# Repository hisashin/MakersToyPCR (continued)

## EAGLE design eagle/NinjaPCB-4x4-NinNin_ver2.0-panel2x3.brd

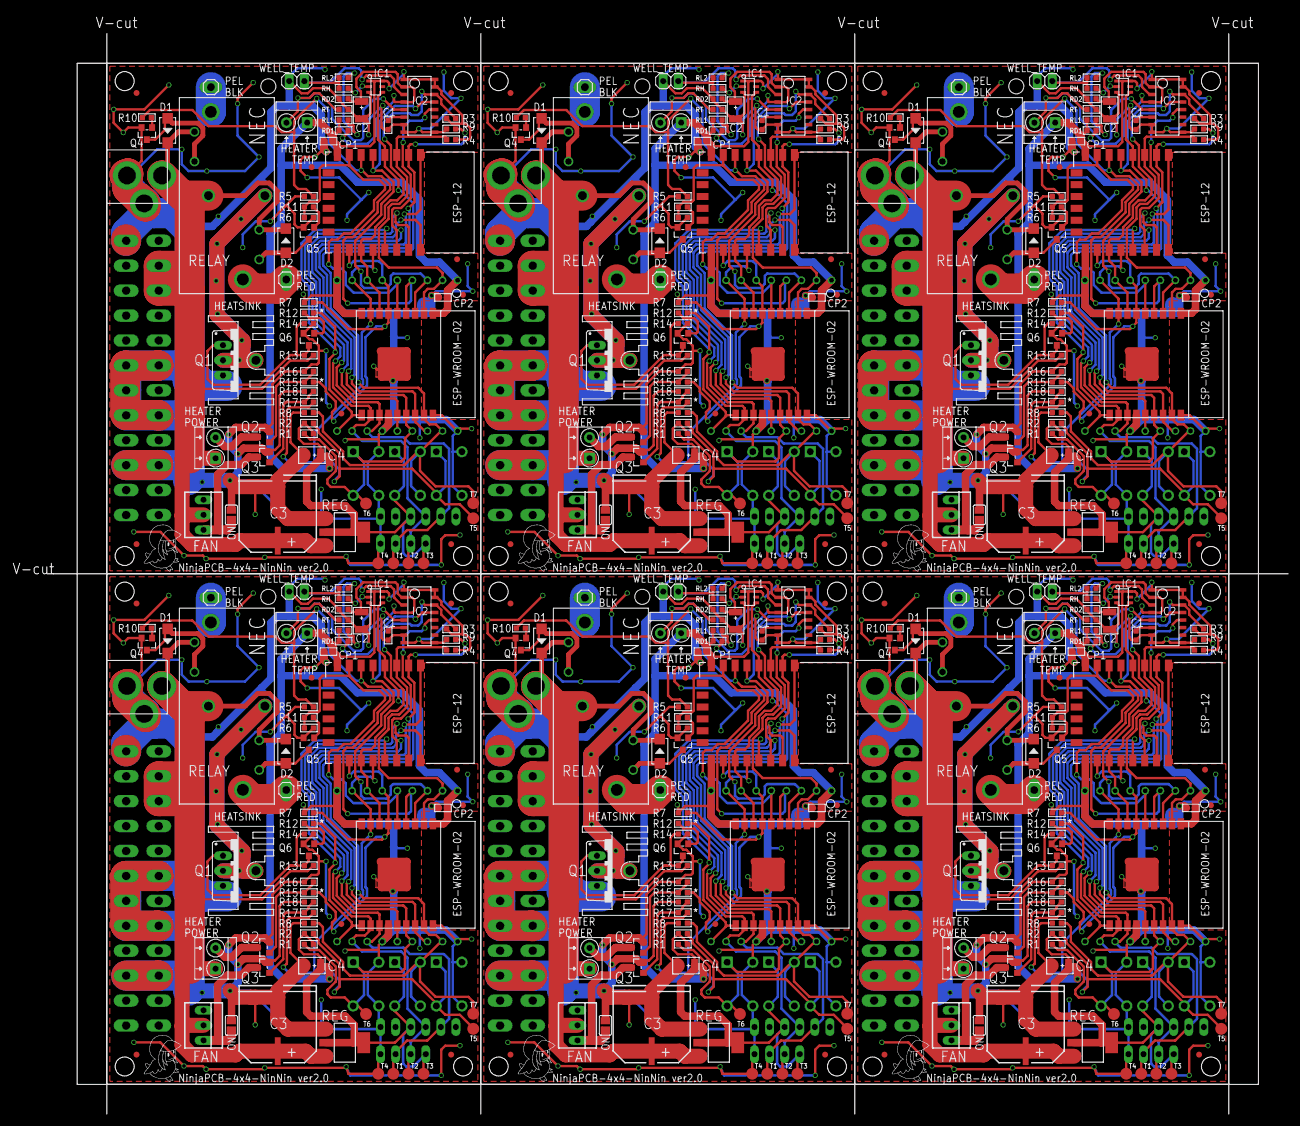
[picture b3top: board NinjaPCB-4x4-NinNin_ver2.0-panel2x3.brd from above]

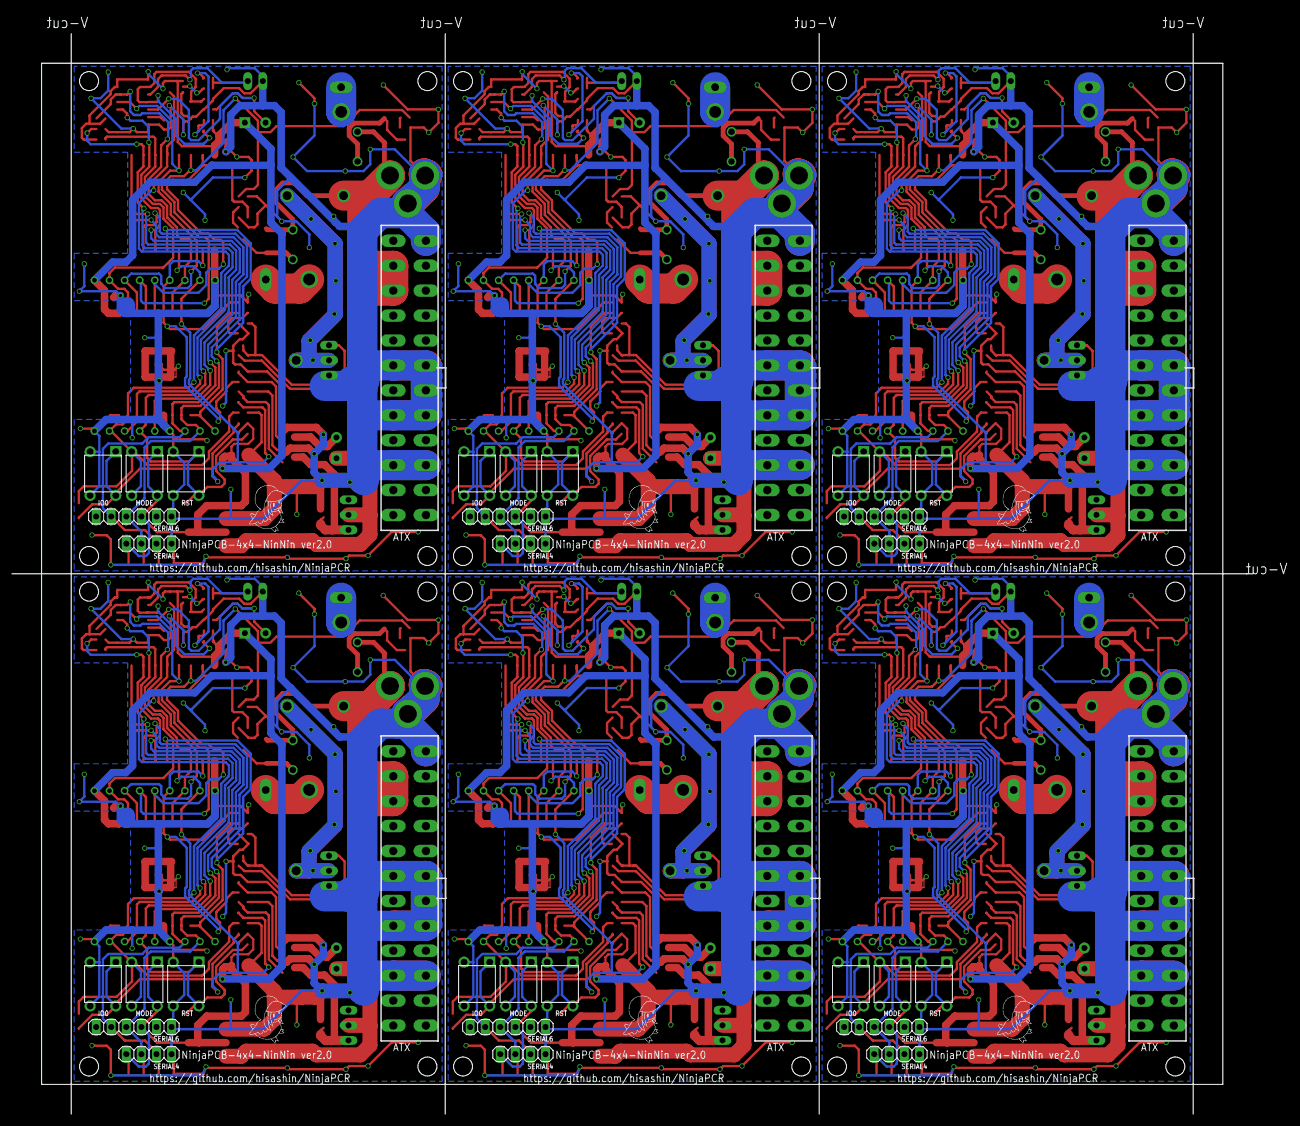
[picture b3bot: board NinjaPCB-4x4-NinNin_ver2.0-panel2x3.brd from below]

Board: 2 copper layers, 209.0 x 182.0 mm, 462 parts (42 on the bottom side), 216 nets.

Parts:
ATX, ATX1, ATX2, ATX3, ATX4, ATX5: ATX24NH; ATX24
C1, C7, C11, C15, C19, C23: 100nf; C0603
C2, C4, C5, C8, C9, C12, C13, C16, C17, C20, C21, C24: 22uf; AVX-B
C3, C6, C10, C14, C18, C22: CAP_SMDAL_1000UF_25V; CAP_SMD_AL_D125
CP1, CP2, CP3, CP4, CP5, CP6, CP7, CP8, CP9, CP10, CP11, CP12: 100nf; C0603
D1, D2, D3, D4, D5, D6, D7, D8, D9, D10, D11, D12: 1N4007; DO-214AC
ESP-1, ESP-2, ESP-3, ESP-4, ESP-5, ESP-12: ESP-12F
ESP-WROOM-01, ESP-WROOM-02, ESP-WROOM-03, ESP-WROOM-04, ESP-WROOM-05, ESP-WROOM-06: ESP-WROOM-02
ESP-WROOM-02-BREAK, ESP-WROOM-02-BREAK1, ESP-WROOM-02-BREAK2, ESP-WROOM-02-BREAK3, ESP-WROOM-02-BREAK4, ESP-WROOM-02-BREAK5: ESP-WROOM-02-BREAKND; ESP-WROOM-02-BREAK-NODETAIL
FAN, FAN1, FAN2, FAN3, FAN4, FAN5: 22-23-2031
FAN_ON, FAN_ON1, FAN_ON2, FAN_ON3, FAN_ON4, FAN_ON5: SJ
HEATER_POWER, HEATER_POWER1, HEATER_POWER2, HEATER_POWER3, HEATER_POWER4, HEATER_POWER5: H2-3.5-7.0X7.0MM
HEATER_TEMP, HEATER_TEMP1, HEATER_TEMP2, HEATER_TEMP3, HEATER_TEMP4, HEATER_TEMP5: H2-3.5-7.0X7.0MM
HEATSINK, HEATSINK1, HEATSINK2, HEATSINK3, HEATSINK4, HEATSINK5: HEAT111PB015; HEAT11PB015
IC1, IC4, IC6, IC8, IC10, IC12: ANALOGSW_AD_SOT23-6; SOT-23-6
IC2, IC3, IC5, IC7, IC9, IC11: NAU7802; SOP-16
IO0, IO1, IO2, IO3, IO4, IO5: SW4-6.0X6.0X5.0MM
JACK, JACK1, JACK2, JACK3, JACK4, JACK5: 2.1MMJACKTHM-NOOUT; PJ-102A-NOOUT
MODE, MODE1, MODE2, MODE3, MODE4, MODE5: SW4-6.0X6.0X5.0MM
PEL_BLK, PEL_BLK1, PEL_BLK2, PEL_BLK3, PEL_BLK4, PEL_BLK5: 1X01LONG
PEL_RED, PEL_RED1, PEL_RED2, PEL_RED3, PEL_RED4, PEL_RED5: 1X01LONG
Q1, Q12, Q18, Q24, Q30, Q36: IRLB3813PBF; TO220BV
Q2, Q3, Q10, Q11, Q16, Q17, Q22, Q23, Q28, Q29, Q34, Q35: CJ2302; SOT-23
Q4, Q5, Q6, Q7, Q8, Q9, Q13, Q14, Q15, Q19, Q20, Q21, Q25, Q26, Q27, Q31, Q32, Q33: S9013; SOT-23
R1, R2, R3, R4, R5, R6, R7, R8, R9, R10, R11, R13, R14, R16, R18, R19, R22, R23, R24, R25, R26, R28, R29, R30, R31, R32, R33, R34, R35, R36, R37, R40, R41, R42, R43, R44, R46, R47, R48, R49, R50, R51, R52, R53, R54, R55, R58, R59, R60, R61, R62, R64, R65, R66, R67, R68, R69, R70, R71, R72, R73, R76, R77, R78, R79, R80, R82, R83, R84, R85, R86, R87, R88, R89, R90, R91, R94, R95, R96, R97, R98, R100, R101, R102, R103, R104, R105, R106, R107, R108: 10K 1/10W; R0603
R12, R15, R17, R20, R21, R27, R38, R39, R45, R56, R57, R63, R74, R75, R81, R92, R93, R99: 1K 1/10W; R0603
RD1, RD2, RD3, RD4, RD5, RD6, RD7, RD8, RD9, RD10, RD11, RD12: 15K HP; R0603
REG, REG1, REG2, REG3, REG4, REG5: CJT1117-3.3-SOT223; SOT-223
RELAY, RELAY1, RELAY2, RELAY3, RELAY4, RELAY5: NEC-RELAY2EP2; NEC-EP2
RH, RH1, RH2, RH3, RH4, RH5: 15K HP; R0603
RL1, RL2, RL3, RL4, RL5, RL6, RL7, RL8, RL9, RL10, RL11, RL12: 15K HP; R0603
RST, RST1, RST2, RST3, RST4, RST5: SW4-6.0X6.0X5.0MM
RT, RT1, RT2, RT3, RT4, RT5: 15K HP; R0603
SERIAL1, SERIAL3, SERIAL6, SERIAL7, SERIAL9, SERIAL11: 1X06
SERIAL2, SERIAL4, SERIAL5, SERIAL8, SERIAL10, SERIAL12: 1X04
T1, T2, T3, T4, T5, T6, T7, T8, T9, T10, T11, T12, T13, T14, T15, T16, T17, T18, T19, T20, T21, T22, T23, T24, T25, T26, T27, T28, T29, T30, T31, T32, T33, T34, T35, T36, T37, T38, T39, T40, T41, T42: TPTP20R; TP20R
U$1, U$2, U$15, U$16, U$25, U$26, U$35, U$36, U$45, U$46, U$55, U$56: TORI_0.25
U$3, U$4, U$5, U$6, U$7, U$8, U$9, U$10, U$11, U$12, U$13, U$14, U$17, U$18, U$19, U$20, U$21, U$22, U$23, U$24, U$27, U$28, U$29, U$30, U$31, U$32, U$33, U$34, U$37, U$38, U$39, U$40, U$41, U$42, U$43, U$44, U$47, U$48, U$49, U$50, U$51, U$52, U$53, U$54, U$57, U$58, U$59, U$60: FIDUCIAL; FIDUCIAL_1MM
WELL_TEMP, WELL_TEMP1, WELL_TEMP2, WELL_TEMP3, WELL_TEMP4, WELL_TEMP5: 1X02

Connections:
3V1: C5.+, CP3.1, CP4.2, ESP-1.8, ESP-WROOM-01.P$1, ESP-WROOM-02-BREAK1.P$1, HEATER_TEMP1.1, IC3.P$1, IC3.P$15, IC3.P$16, IC4.P$1, IC4.P$6, MODE1.1, MODE1.4, R19.1, R23.1, R32.1, R35.1, RD3.2, REG1.2, REG1.TER, RL4.1, SERIAL1.4, SERIAL2.1, T10.TP
3V2: C9.+, CP5.1, CP6.2, ESP-2.8, ESP-WROOM-02-BREAK2.P$1, ESP-WROOM-03.P$1, HEATER_TEMP2.1, IC5.P$1, IC5.P$15, IC5.P$16, IC6.P$1, IC6.P$6, MODE2.1, MODE2.4, R37.1, R41.1, R50.1, R53.1, RD5.2, REG2.2, REG2.TER, RL6.1, SERIAL3.4, SERIAL5.1, T17.TP
3V3: C4.+, CP1.1, CP2.2, ESP-12.8, ESP-WROOM-02.P$1, ESP-WROOM-02-BREAK.P$1, HEATER_TEMP.1, IC1.P$1, IC1.P$6, IC2.P$1, IC2.P$15, IC2.P$16, MODE.1, MODE.4, R1.1, R2.1, R3.1, R4.1, RD1.2, REG.2, REG.TER, RL1.1, SERIAL4.1, SERIAL6.4, T3.TP
3V4: C13.+, CP7.1, CP8.2, ESP-3.8, ESP-WROOM-02-BREAK3.P$1, ESP-WROOM-04.P$1, HEATER_TEMP3.1, IC7.P$1, IC7.P$15, IC7.P$16, IC8.P$1, IC8.P$6, MODE3.1, MODE3.4, R55.1, R59.1, R68.1, R71.1, RD7.2, REG3.2, REG3.TER, RL8.1, SERIAL7.4, SERIAL8.1, T24.TP
3V5: C17.+, CP9.1, CP10.2, ESP-4.8, ESP-WROOM-02-BREAK4.P$1, ESP-WROOM-05.P$1, HEATER_TEMP4.1, IC9.P$1, IC9.P$15, IC9.P$16, IC10.P$1, IC10.P$6, MODE4.1, MODE4.4, R73.1, R77.1, R86.1, R89.1, RD9.2, REG4.2, REG4.TER, RL10.1, SERIAL9.4, SERIAL10.1, T31.TP
3V6: C21.+, CP11.1, CP12.2, ESP-5.8, ESP-WROOM-02-BREAK5.P$1, ESP-WROOM-06.P$1, HEATER_TEMP5.1, IC11.P$1, IC11.P$15, IC11.P$16, IC12.P$1, IC12.P$6, MODE5.1, MODE5.4, R91.1, R95.1, R104.1, R107.1, RD11.2, REG5.2, REG5.TER, RL12.1, SERIAL11.4, SERIAL12.1, T38.TP
12V: ATX.10, ATX.11, C3.P$P, D1.2, D2.2, FAN.2, HEATER_POWER.1, JACK.TIP, R13.2, REG.3, RELAY.P$2, RELAY.P$4, RELAY.P$6
12V1: ATX1.10, ATX1.11, C6.P$P, D3.2, D4.2, FAN1.2, HEATER_POWER1.1, JACK1.TIP, R28.2, REG1.3, RELAY1.P$2, RELAY1.P$4, RELAY1.P$6
12V2: ATX2.10, ATX2.11, C10.P$P, D5.2, D6.2, FAN2.2, HEATER_POWER2.1, JACK2.TIP, R46.2, REG2.3, RELAY2.P$2, RELAY2.P$4, RELAY2.P$6
12V3: ATX3.10, ATX3.11, C14.P$P, D7.2, D8.2, FAN3.2, HEATER_POWER3.1, JACK3.TIP, R64.2, REG3.3, RELAY3.P$2, RELAY3.P$4, RELAY3.P$6
12V4: ATX4.10, ATX4.11, C18.P$P, D9.2, D10.2, FAN4.2, HEATER_POWER4.1, JACK4.TIP, R82.2, REG4.3, RELAY4.P$2, RELAY4.P$4, RELAY4.P$6
12V5: ATX5.10, ATX5.11, C22.P$P, D11.2, D12.2, FAN5.2, HEATER_POWER5.1, JACK5.TIP, R100.2, REG5.3, RELAY5.P$2, RELAY5.P$4, RELAY5.P$6
DIVIDED: C2.+, IC2.P$2, IC2.P$4, RD1.1, RD2.1
DIVIDED1: C8.+, IC3.P$2, IC3.P$4, RD3.1, RD4.1
DIVIDED2: C12.+, IC5.P$2, IC5.P$4, RD5.1, RD6.1
DIVIDED3: C16.+, IC7.P$2, IC7.P$4, RD7.1, RD8.1
DIVIDED4: C20.+, IC9.P$2, IC9.P$4, RD9.1, RD10.1
DIVIDED5: C24.+, IC11.P$2, IC11.P$4, RD11.1, RD12.1
DRDY: ESP-12.20, ESP-WROOM-02.P$14, ESP-WROOM-02-BREAK.P$14, IC2.P$12
DRDY1: ESP-1.20, ESP-WROOM-01.P$14, ESP-WROOM-02-BREAK1.P$14, IC3.P$12
DRDY2: ESP-2.20, ESP-WROOM-02-BREAK2.P$14, ESP-WROOM-03.P$14, IC5.P$12
DRDY3: ESP-3.20, ESP-WROOM-02-BREAK3.P$14, ESP-WROOM-04.P$14, IC7.P$12
DRDY4: ESP-4.20, ESP-WROOM-02-BREAK4.P$14, ESP-WROOM-05.P$14, IC9.P$12
DRDY5: ESP-5.20, ESP-WROOM-02-BREAK5.P$14, ESP-WROOM-06.P$14, IC11.P$12
EN: ESP-12.3, ESP-WROOM-02.P$2, ESP-WROOM-02-BREAK.P$2, R4.2
EN1: ESP-1.3, ESP-WROOM-01.P$2, ESP-WROOM-02-BREAK1.P$2, R32.2
EN2: ESP-2.3, ESP-WROOM-02-BREAK2.P$2, ESP-WROOM-03.P$2, R50.2
EN3: ESP-3.3, ESP-WROOM-02-BREAK3.P$2, ESP-WROOM-04.P$2, R68.2
EN4: ESP-4.3, ESP-WROOM-02-BREAK4.P$2, ESP-WROOM-05.P$2, R86.2
EN5: ESP-5.3, ESP-WROOM-02-BREAK5.P$2, ESP-WROOM-06.P$2, R104.2
FAN: ESP-12.18, ESP-WROOM-02.P$8, ESP-WROOM-02-BREAK.P$8, IO0.1, IO0.4, R2.2, R17.1, T5.TP
FAN1: ESP-1.18, ESP-WROOM-01.P$8, ESP-WROOM-02-BREAK1.P$8, IO1.1, IO1.4, R20.1, R23.2, T12.TP
FAN2: ESP-2.18, ESP-WROOM-02-BREAK2.P$8, ESP-WROOM-03.P$8, IO2.1, IO2.4, R38.1, R41.2, T19.TP
FAN3: ESP-3.18, ESP-WROOM-02-BREAK3.P$8, ESP-WROOM-04.P$8, IO3.1, IO3.4, R56.1, R59.2, T26.TP
FAN4: ESP-4.18, ESP-WROOM-02-BREAK4.P$8, ESP-WROOM-05.P$8, IO4.1, IO4.4, R74.1, R77.2, T33.TP
FAN5: ESP-5.18, ESP-WROOM-02-BREAK5.P$8, ESP-WROOM-06.P$8, IO5.1, IO5.4, R92.1, R95.2, T40.TP
GND: ATX.3, ATX.5, ATX.7, ATX.15, ATX.17, ATX.18, ATX.19, ATX.24, C1.1, C2.-, C3.P$M, C4.-, CP1.2, CP2.1, ESP-12.15, ESP-WROOM-02.P$9, ESP-WROOM-02.P$13, ESP-WROOM-02.P$18, ESP-WROOM-02.P$19, ESP-WROOM-02-BREAK.P$9, ESP-WROOM-02-BREAK.P$13, ESP-WROOM-02-BREAK.P$18, FAN_ON.1, IC1.P$3, IC2.P$7, IC2.P$8, IC2.P$9, IO0.2, IO0.3, JACK.RING, JACK.RING_SW, Q1.S, Q2.2, Q3.2, Q4.2, Q5.2, Q6.2, R5.1, R6.1, R7.1, R8.1, R9.1, R14.1, R16.1, R18.1, RD2.2, REG.1, RST.2, RST.3, RT.2, SERIAL4.4, SERIAL6.6, T4.TP, WELL_TEMP.2
GND1: ATX1.3, ATX1.5, ATX1.7, ATX1.15, ATX1.17, ATX1.18, ATX1.19, ATX1.24, C5.-, C6.P$M, C7.1, C8.-, CP3.2, CP4.1, ESP-1.15, ESP-WROOM-01.P$9, ESP-WROOM-01.P$13, ESP-WROOM-01.P$18, ESP-WROOM-01.P$19, ESP-WROOM-02-BREAK1.P$9, ESP-WROOM-02-BREAK1.P$13, ESP-WROOM-02-BREAK1.P$18, FAN_ON1.1, IC3.P$7, IC3.P$8, IC3.P$9, IC4.P$3, IO1.2, IO1.3, JACK1.RING, JACK1.RING_SW, Q7.2, Q8.2, Q9.2, Q10.2, Q11.2, Q12.S, R22.1, R24.1, R25.1, R26.1, R29.1, R33.1, R34.1, R36.1, RD4.2, REG1.1, RST1.2, RST1.3, RT1.2, SERIAL1.6, SERIAL2.4, T11.TP, WELL_TEMP1.2
GND2: ATX2.3, ATX2.5, ATX2.7, ATX2.15, ATX2.17, ATX2.18, ATX2.19, ATX2.24, C9.-, C10.P$M, C11.1, C12.-, CP5.2, CP6.1, ESP-2.15, ESP-WROOM-02-BREAK2.P$9, ESP-WROOM-02-BREAK2.P$13, ESP-WROOM-02-BREAK2.P$18, ESP-WROOM-03.P$9, ESP-WROOM-03.P$13, ESP-WROOM-03.P$18, ESP-WROOM-03.P$19, FAN_ON2.1, IC5.P$7, IC5.P$8, IC5.P$9, IC6.P$3, IO2.2, IO2.3, JACK2.RING, JACK2.RING_SW, Q13.2, Q14.2, Q15.2, Q16.2, Q17.2, Q18.S, R40.1, R42.1, R43.1, R44.1, R47.1, R51.1, R52.1, R54.1, RD6.2, REG2.1, RST2.2, RST2.3, RT2.2, SERIAL3.6, SERIAL5.4, T18.TP, WELL_TEMP2.2
GND3: ATX3.3, ATX3.5, ATX3.7, ATX3.15, ATX3.17, ATX3.18, ATX3.19, ATX3.24, C13.-, C14.P$M, C15.1, C16.-, CP7.2, CP8.1, ESP-3.15, ESP-WROOM-02-BREAK3.P$9, ESP-WROOM-02-BREAK3.P$13, ESP-WROOM-02-BREAK3.P$18, ESP-WROOM-04.P$9, ESP-WROOM-04.P$13, ESP-WROOM-04.P$18, ESP-WROOM-04.P$19, FAN_ON3.1, IC7.P$7, IC7.P$8, IC7.P$9, IC8.P$3, IO3.2, IO3.3, JACK3.RING, JACK3.RING_SW, Q19.2, Q20.2, Q21.2, Q22.2, Q23.2, Q24.S, R58.1, R60.1, R61.1, R62.1, R65.1, R69.1, R70.1, R72.1, RD8.2, REG3.1, RST3.2, RST3.3, RT3.2, SERIAL7.6, SERIAL8.4, T25.TP, WELL_TEMP3.2
GND4: ATX4.3, ATX4.5, ATX4.7, ATX4.15, ATX4.17, ATX4.18, ATX4.19, ATX4.24, C17.-, C18.P$M, C19.1, C20.-, CP9.2, CP10.1, ESP-4.15, ESP-WROOM-02-BREAK4.P$9, ESP-WROOM-02-BREAK4.P$13, ESP-WROOM-02-BREAK4.P$18, ESP-WROOM-05.P$9, ESP-WROOM-05.P$13, ESP-WROOM-05.P$18, ESP-WROOM-05.P$19, FAN_ON4.1, IC9.P$7, IC9.P$8, IC9.P$9, IC10.P$3, IO4.2, IO4.3, JACK4.RING, JACK4.RING_SW, Q25.2, Q26.2, Q27.2, Q28.2, Q29.2, Q30.S, R76.1, R78.1, R79.1, R80.1, R83.1, R87.1, R88.1, R90.1, RD10.2, REG4.1, RST4.2, RST4.3, RT4.2, SERIAL9.6, SERIAL10.4, T32.TP, WELL_TEMP4.2
GND5: ATX5.3, ATX5.5, ATX5.7, ATX5.15, ATX5.17, ATX5.18, ATX5.19, ATX5.24, C21.-, C22.P$M, C23.1, C24.-, CP11.2, CP12.1, ESP-5.15, ESP-WROOM-02-BREAK5.P$9, ESP-WROOM-02-BREAK5.P$13, ESP-WROOM-02-BREAK5.P$18, ESP-WROOM-06.P$9, ESP-WROOM-06.P$13, ESP-WROOM-06.P$18, ESP-WROOM-06.P$19, FAN_ON5.1, IC11.P$7, IC11.P$8, IC11.P$9, IC12.P$3, IO5.2, IO5.3, JACK5.RING, JACK5.RING_SW, Q31.2, Q32.2, Q33.2, Q34.2, Q35.2, Q36.S, R94.1, R96.1, R97.1, R98.1, R101.1, R105.1, R106.1, R108.1, RD12.2, REG5.1, RST5.2, RST5.3, RT5.2, SERIAL11.6, SERIAL12.4, T39.TP, WELL_TEMP5.2
HEATER: ESP-12.16, ESP-WROOM-02.P$6, ESP-WROOM-02-BREAK.P$6, R7.2, R15.1
HEATER1: ESP-1.16, ESP-WROOM-01.P$6, ESP-WROOM-02-BREAK1.P$6, R21.1, R24.2
HEATER2: ESP-2.16, ESP-WROOM-02-BREAK2.P$6, ESP-WROOM-03.P$6, R39.1, R42.2
HEATER3: ESP-3.16, ESP-WROOM-02-BREAK3.P$6, ESP-WROOM-04.P$6, R57.1, R60.2
HEATER4: ESP-4.16, ESP-WROOM-02-BREAK4.P$6, ESP-WROOM-05.P$6, R75.1, R78.2
HEATER5: ESP-5.16, ESP-WROOM-02-BREAK5.P$6, ESP-WROOM-06.P$6, R93.1, R96.2
HEATER_TEMP: HEATER_TEMP.2, IC2.P$5, RT.1
HEATER_TEMP1: HEATER_TEMP1.2, IC3.P$5, RT1.1
HEATER_TEMP2: HEATER_TEMP2.2, IC5.P$5, RT2.1
HEATER_TEMP3: HEATER_TEMP3.2, IC7.P$5, RT3.1
HEATER_TEMP4: HEATER_TEMP4.2, IC9.P$5, RT4.1
HEATER_TEMP5: HEATER_TEMP5.2, IC11.P$5, RT5.1
HIGH_TEMP: ESP-12.4, ESP-WROOM-02.P$17, ESP-WROOM-02-BREAK.P$17, IC1.P$4, MODE.2, MODE.3, R8.2, T7.TP
HIGH_TEMP1: ESP-1.4, ESP-WROOM-01.P$17, ESP-WROOM-02-BREAK1.P$17, IC4.P$4, MODE1.2, MODE1.3, R22.2, T14.TP
HIGH_TEMP2: ESP-2.4, ESP-WROOM-02-BREAK2.P$17, ESP-WROOM-03.P$17, IC6.P$4, MODE2.2, MODE2.3, R40.2, T21.TP
HIGH_TEMP3: ESP-3.4, ESP-WROOM-02-BREAK3.P$17, ESP-WROOM-04.P$17, IC8.P$4, MODE3.2, MODE3.3, R58.2, T28.TP
HIGH_TEMP4: ESP-4.4, ESP-WROOM-02-BREAK4.P$17, ESP-WROOM-05.P$17, IC10.P$4, MODE4.2, MODE4.3, R76.2, T35.TP
HIGH_TEMP5: ESP-5.4, ESP-WROOM-02-BREAK5.P$17, ESP-WROOM-06.P$17, IC12.P$4, MODE5.2, MODE5.3, R94.2, T42.TP
MODE: ESP-12.2, ESP-WROOM-02.P$16, ESP-WROOM-02-BREAK.P$16, R9.2
MODE1: ESP-1.2, ESP-WROOM-01.P$16, ESP-WROOM-02-BREAK1.P$16, R36.2
MODE2: ESP-2.2, ESP-WROOM-02-BREAK2.P$16, ESP-WROOM-03.P$16, R54.2
MODE3: ESP-3.2, ESP-WROOM-02-BREAK3.P$16, ESP-WROOM-04.P$16, R72.2
MODE4: ESP-4.2, ESP-WROOM-02-BREAK4.P$16, ESP-WROOM-05.P$16, R90.2
MODE5: ESP-5.2, ESP-WROOM-02-BREAK5.P$16, ESP-WROOM-06.P$16, R108.2
unnamed: RL1.2, RL2.1
unnamed: HEATER_POWER.2, Q2.3
unnamed: HEATSINK.P$1, Q1.D, RELAY.P$5
unnamed: FAN.3, FAN_ON.2, Q3.3
unnamed: Q1.G, Q6.3, R13.1, R14.2
unnamed: PEL_RED.1, RELAY.P$8
unnamed: PEL_BLK.1, RELAY.P$1
unnamed: Q3.1, R17.2, R18.2
unnamed: HEATER_POWER1.2, Q10.3
unnamed: FAN1.3, FAN_ON1.2, Q11.3
unnamed: C7.2, IC3.P$6
unnamed: IC4.P$2, RH1.1
unnamed: Q10.1, R21.2, R25.2
unnamed: HEATSINK1.P$1, Q12.D, RELAY1.P$5
unnamed: Q9.3, Q12.G, R28.1, R29.2
unnamed: Q9.1, R27.2
unnamed: D3.1, Q7.3, RELAY1.P$3
unnamed: D4.1, Q8.3, RELAY1.P$7
unnamed: Q7.1, R30.2
unnamed: Q8.1, R31.1
unnamed: PEL_RED1.1, RELAY1.P$8
unnamed: PEL_BLK1.1, RELAY1.P$1
unnamed: RL3.1, RL4.2
unnamed: Q11.1, R20.2, R26.2
unnamed: HEATER_POWER2.2, Q16.3
unnamed: FAN2.3, FAN_ON2.2, Q17.3
unnamed: IC1.P$2, RH.1
unnamed: C11.2, IC5.P$6
unnamed: IC6.P$2, RH2.1
unnamed: Q6.1, R12.2
unnamed: Q16.1, R39.2, R43.2
unnamed: Q2.1, R15.2, R16.2
unnamed: D1.1, Q4.3, RELAY.P$3
unnamed: Q4.1, R10.2
unnamed: Q5.1, R11.1
unnamed: D2.1, Q5.3, RELAY.P$7
unnamed: HEATSINK2.P$1, Q18.D, RELAY2.P$5
unnamed: Q15.3, Q18.G, R46.1, R47.2
unnamed: Q15.1, R45.2
unnamed: D5.1, Q13.3, RELAY2.P$3
unnamed: D6.1, Q14.3, RELAY2.P$7
unnamed: Q13.1, R48.2
unnamed: Q14.1, R49.1
unnamed: PEL_RED2.1, RELAY2.P$8
unnamed: PEL_BLK2.1, RELAY2.P$1
unnamed: RL5.1, RL6.2
unnamed: Q17.1, R38.2, R44.2
unnamed: HEATER_POWER3.2, Q22.3
unnamed: FAN3.3, FAN_ON3.2, Q23.3
unnamed: C15.2, IC7.P$6
unnamed: IC8.P$2, RH3.1
unnamed: Q22.1, R57.2, R61.2
unnamed: HEATSINK3.P$1, Q24.D, RELAY3.P$5
unnamed: Q21.3, Q24.G, R64.1, R65.2
unnamed: Q21.1, R63.2
unnamed: D7.1, Q19.3, RELAY3.P$3
unnamed: D8.1, Q20.3, RELAY3.P$7
unnamed: Q19.1, R66.2
unnamed: Q20.1, R67.1
unnamed: PEL_RED3.1, RELAY3.P$8
unnamed: PEL_BLK3.1, RELAY3.P$1
unnamed: RL7.1, RL8.2
unnamed: Q23.1, R56.2, R62.2
unnamed: HEATER_POWER4.2, Q28.3
unnamed: FAN4.3, FAN_ON4.2, Q29.3
unnamed: C19.2, IC9.P$6
unnamed: IC10.P$2, RH4.1
unnamed: Q28.1, R75.2, R79.2
unnamed: HEATSINK4.P$1, Q30.D, RELAY4.P$5
unnamed: Q27.3, Q30.G, R82.1, R83.2
unnamed: Q27.1, R81.2
unnamed: D9.1, Q25.3, RELAY4.P$3
unnamed: D10.1, Q26.3, RELAY4.P$7
unnamed: Q25.1, R84.2
unnamed: Q26.1, R85.1
unnamed: PEL_RED4.1, RELAY4.P$8
unnamed: PEL_BLK4.1, RELAY4.P$1
unnamed: RL9.1, RL10.2
unnamed: Q29.1, R74.2, R80.2
unnamed: HEATER_POWER5.2, Q34.3
unnamed: FAN5.3, FAN_ON5.2, Q35.3
unnamed: C23.2, IC11.P$6
unnamed: IC12.P$2, RH5.1
unnamed: Q34.1, R93.2, R97.2
unnamed: HEATSINK5.P$1, Q36.D, RELAY5.P$5
unnamed: Q33.3, Q36.G, R100.1, R101.2
unnamed: Q33.1, R99.2
unnamed: D11.1, Q31.3, RELAY5.P$3
unnamed: D12.1, Q32.3, RELAY5.P$7
unnamed: Q31.1, R102.2
unnamed: Q32.1, R103.1
unnamed: C1.2, IC2.P$6
unnamed: PEL_RED5.1, RELAY5.P$8
unnamed: PEL_BLK5.1, RELAY5.P$1
unnamed: RL11.1, RL12.2
unnamed: Q35.1, R92.2, R98.2
PEL_PWM: ESP-12.19, ESP-WROOM-02.P$10, ESP-WROOM-02-BREAK.P$10, R12.1
PEL_PWM1: ESP-1.19, ESP-WROOM-01.P$10, ESP-WROOM-02-BREAK1.P$10, R27.1
PEL_PWM2: ESP-2.19, ESP-WROOM-02-BREAK2.P$10, ESP-WROOM-03.P$10, R45.1
PEL_PWM3: ESP-3.19, ESP-WROOM-02-BREAK3.P$10, ESP-WROOM-04.P$10, R63.1
PEL_PWM4: ESP-4.19, ESP-WROOM-02-BREAK4.P$10, ESP-WROOM-05.P$10, R81.1
PEL_PWM5: ESP-5.19, ESP-WROOM-02-BREAK5.P$10, ESP-WROOM-06.P$10, R99.1
PEL_SWA: ESP-12.6, ESP-WROOM-02.P$4, ESP-WROOM-02-BREAK.P$4, R5.2, R10.1
PEL_SWA1: ESP-1.6, ESP-WROOM-01.P$4, ESP-WROOM-02-BREAK1.P$4, R30.1, R33.2
PEL_SWA2: ESP-2.6, ESP-WROOM-02-BREAK2.P$4, ESP-WROOM-03.P$4, R48.1, R51.2
PEL_SWA3: ESP-3.6, ESP-WROOM-02-BREAK3.P$4, ESP-WROOM-04.P$4, R66.1, R69.2
PEL_SWA4: ESP-4.6, ESP-WROOM-02-BREAK4.P$4, ESP-WROOM-05.P$4, R84.1, R87.2
PEL_SWA5: ESP-5.6, ESP-WROOM-02-BREAK5.P$4, ESP-WROOM-06.P$4, R102.1, R105.2
PEL_SWB: ESP-12.7, ESP-WROOM-02.P$5, ESP-WROOM-02-BREAK.P$5, R6.2, R11.2
PEL_SWB1: ESP-1.7, ESP-WROOM-01.P$5, ESP-WROOM-02-BREAK1.P$5, R31.2, R34.2
PEL_SWB2: ESP-2.7, ESP-WROOM-02-BREAK2.P$5, ESP-WROOM-03.P$5, R49.2, R52.2
PEL_SWB3: ESP-3.7, ESP-WROOM-02-BREAK3.P$5, ESP-WROOM-04.P$5, R67.2, R70.2
PEL_SWB4: ESP-4.7, ESP-WROOM-02-BREAK4.P$5, ESP-WROOM-05.P$5, R85.2, R88.2
PEL_SWB5: ESP-5.7, ESP-WROOM-02-BREAK5.P$5, ESP-WROOM-06.P$5, R103.2, R106.2
RESET: ESP-12.1, ESP-WROOM-02.P$15, ESP-WROOM-02-BREAK.P$15, R1.2, RST.1, RST.4, T6.TP
RESET1: ESP-1.1, ESP-WROOM-01.P$15, ESP-WROOM-02-BREAK1.P$15, R19.2, RST1.1, RST1.4, T13.TP
RESET2: ESP-2.1, ESP-WROOM-02-BREAK2.P$15, ESP-WROOM-03.P$15, R37.2, RST2.1, RST2.4, T20.TP
RESET3: ESP-3.1, ESP-WROOM-02-BREAK3.P$15, ESP-WROOM-04.P$15, R55.2, RST3.1, RST3.4, T27.TP
RESET4: ESP-4.1, ESP-WROOM-02-BREAK4.P$15, ESP-WROOM-05.P$15, R73.2, RST4.1, RST4.4, T34.TP
RESET5: ESP-5.1, ESP-WROOM-02-BREAK5.P$15, ESP-WROOM-06.P$15, R91.2, RST5.1, RST5.4, T41.TP
RXD: ESP-12.21, ESP-WROOM-02.P$11, ESP-WROOM-02-BREAK.P$11, SERIAL4.2, SERIAL6.3, T2.TP
RXD1: ESP-1.21, ESP-WROOM-01.P$11, ESP-WROOM-02-BREAK1.P$11, SERIAL1.3, SERIAL2.2, T9.TP
RXD2: ESP-2.21, ESP-WROOM-02-BREAK2.P$11, ESP-WROOM-03.P$11, SERIAL3.3, SERIAL5.2, T16.TP
RXD3: ESP-3.21, ESP-WROOM-02-BREAK3.P$11, ESP-WROOM-04.P$11, SERIAL7.3, SERIAL8.2, T23.TP
RXD4: ESP-4.21, ESP-WROOM-02-BREAK4.P$11, ESP-WROOM-05.P$11, SERIAL9.3, SERIAL10.2, T30.TP
RXD5: ESP-5.21, ESP-WROOM-02-BREAK5.P$11, ESP-WROOM-06.P$11, SERIAL11.3, SERIAL12.2, T37.TP
SCLK: ESP-12.5, ESP-WROOM-02.P$3, ESP-WROOM-02-BREAK.P$3, IC2.P$13
SCLK1: ESP-1.5, ESP-WROOM-01.P$3, ESP-WROOM-02-BREAK1.P$3, IC3.P$13
SCLK2: ESP-2.5, ESP-WROOM-02-BREAK2.P$3, ESP-WROOM-03.P$3, IC5.P$13
SCLK3: ESP-3.5, ESP-WROOM-02-BREAK3.P$3, ESP-WROOM-04.P$3, IC7.P$13
SCLK4: ESP-4.5, ESP-WROOM-02-BREAK4.P$3, ESP-WROOM-05.P$3, IC9.P$13
SCLK5: ESP-5.5, ESP-WROOM-02-BREAK5.P$3, ESP-WROOM-06.P$3, IC11.P$13
SDIO: ESP-12.17, ESP-WROOM-02.P$7, ESP-WROOM-02-BREAK.P$7, IC2.P$14, R3.2
SDIO1: ESP-1.17, ESP-WROOM-01.P$7, ESP-WROOM-02-BREAK1.P$7, IC3.P$14, R35.2
SDIO2: ESP-2.17, ESP-WROOM-02-BREAK2.P$7, ESP-WROOM-03.P$7, IC5.P$14, R53.2
SDIO3: ESP-3.17, ESP-WROOM-02-BREAK3.P$7, ESP-WROOM-04.P$7, IC7.P$14, R71.2
SDIO4: ESP-4.17, ESP-WROOM-02-BREAK4.P$7, ESP-WROOM-05.P$7, IC9.P$14, R89.2
SDIO5: ESP-5.17, ESP-WROOM-02-BREAK5.P$7, ESP-WROOM-06.P$7, IC11.P$14, R107.2
TXD: ESP-12.22, ESP-WROOM-02.P$12, ESP-WROOM-02-BREAK.P$12, SERIAL4.3, SERIAL6.2, T1.TP
TXD1: ESP-1.22, ESP-WROOM-01.P$12, ESP-WROOM-02-BREAK1.P$12, SERIAL1.2, SERIAL2.3, T8.TP
TXD2: ESP-2.22, ESP-WROOM-02-BREAK2.P$12, ESP-WROOM-03.P$12, SERIAL3.2, SERIAL5.3, T15.TP
TXD3: ESP-3.22, ESP-WROOM-02-BREAK3.P$12, ESP-WROOM-04.P$12, SERIAL7.2, SERIAL8.3, T22.TP
TXD4: ESP-4.22, ESP-WROOM-02-BREAK4.P$12, ESP-WROOM-05.P$12, SERIAL9.2, SERIAL10.3, T29.TP
TXD5: ESP-5.22, ESP-WROOM-02-BREAK5.P$12, ESP-WROOM-06.P$12, SERIAL11.2, SERIAL12.3, T36.TP
WELL_TEMP: IC2.P$3, RH.2, RL2.2, WELL_TEMP.1
WELL_TEMP1: IC3.P$3, RH1.2, RL3.2, WELL_TEMP1.1
WELL_TEMP2: IC5.P$3, RH2.2, RL5.2, WELL_TEMP2.1
WELL_TEMP3: IC7.P$3, RH3.2, RL7.2, WELL_TEMP3.1
WELL_TEMP4: IC9.P$3, RH4.2, RL9.2, WELL_TEMP4.1
WELL_TEMP5: IC11.P$3, RH5.2, RL11.2, WELL_TEMP5.1

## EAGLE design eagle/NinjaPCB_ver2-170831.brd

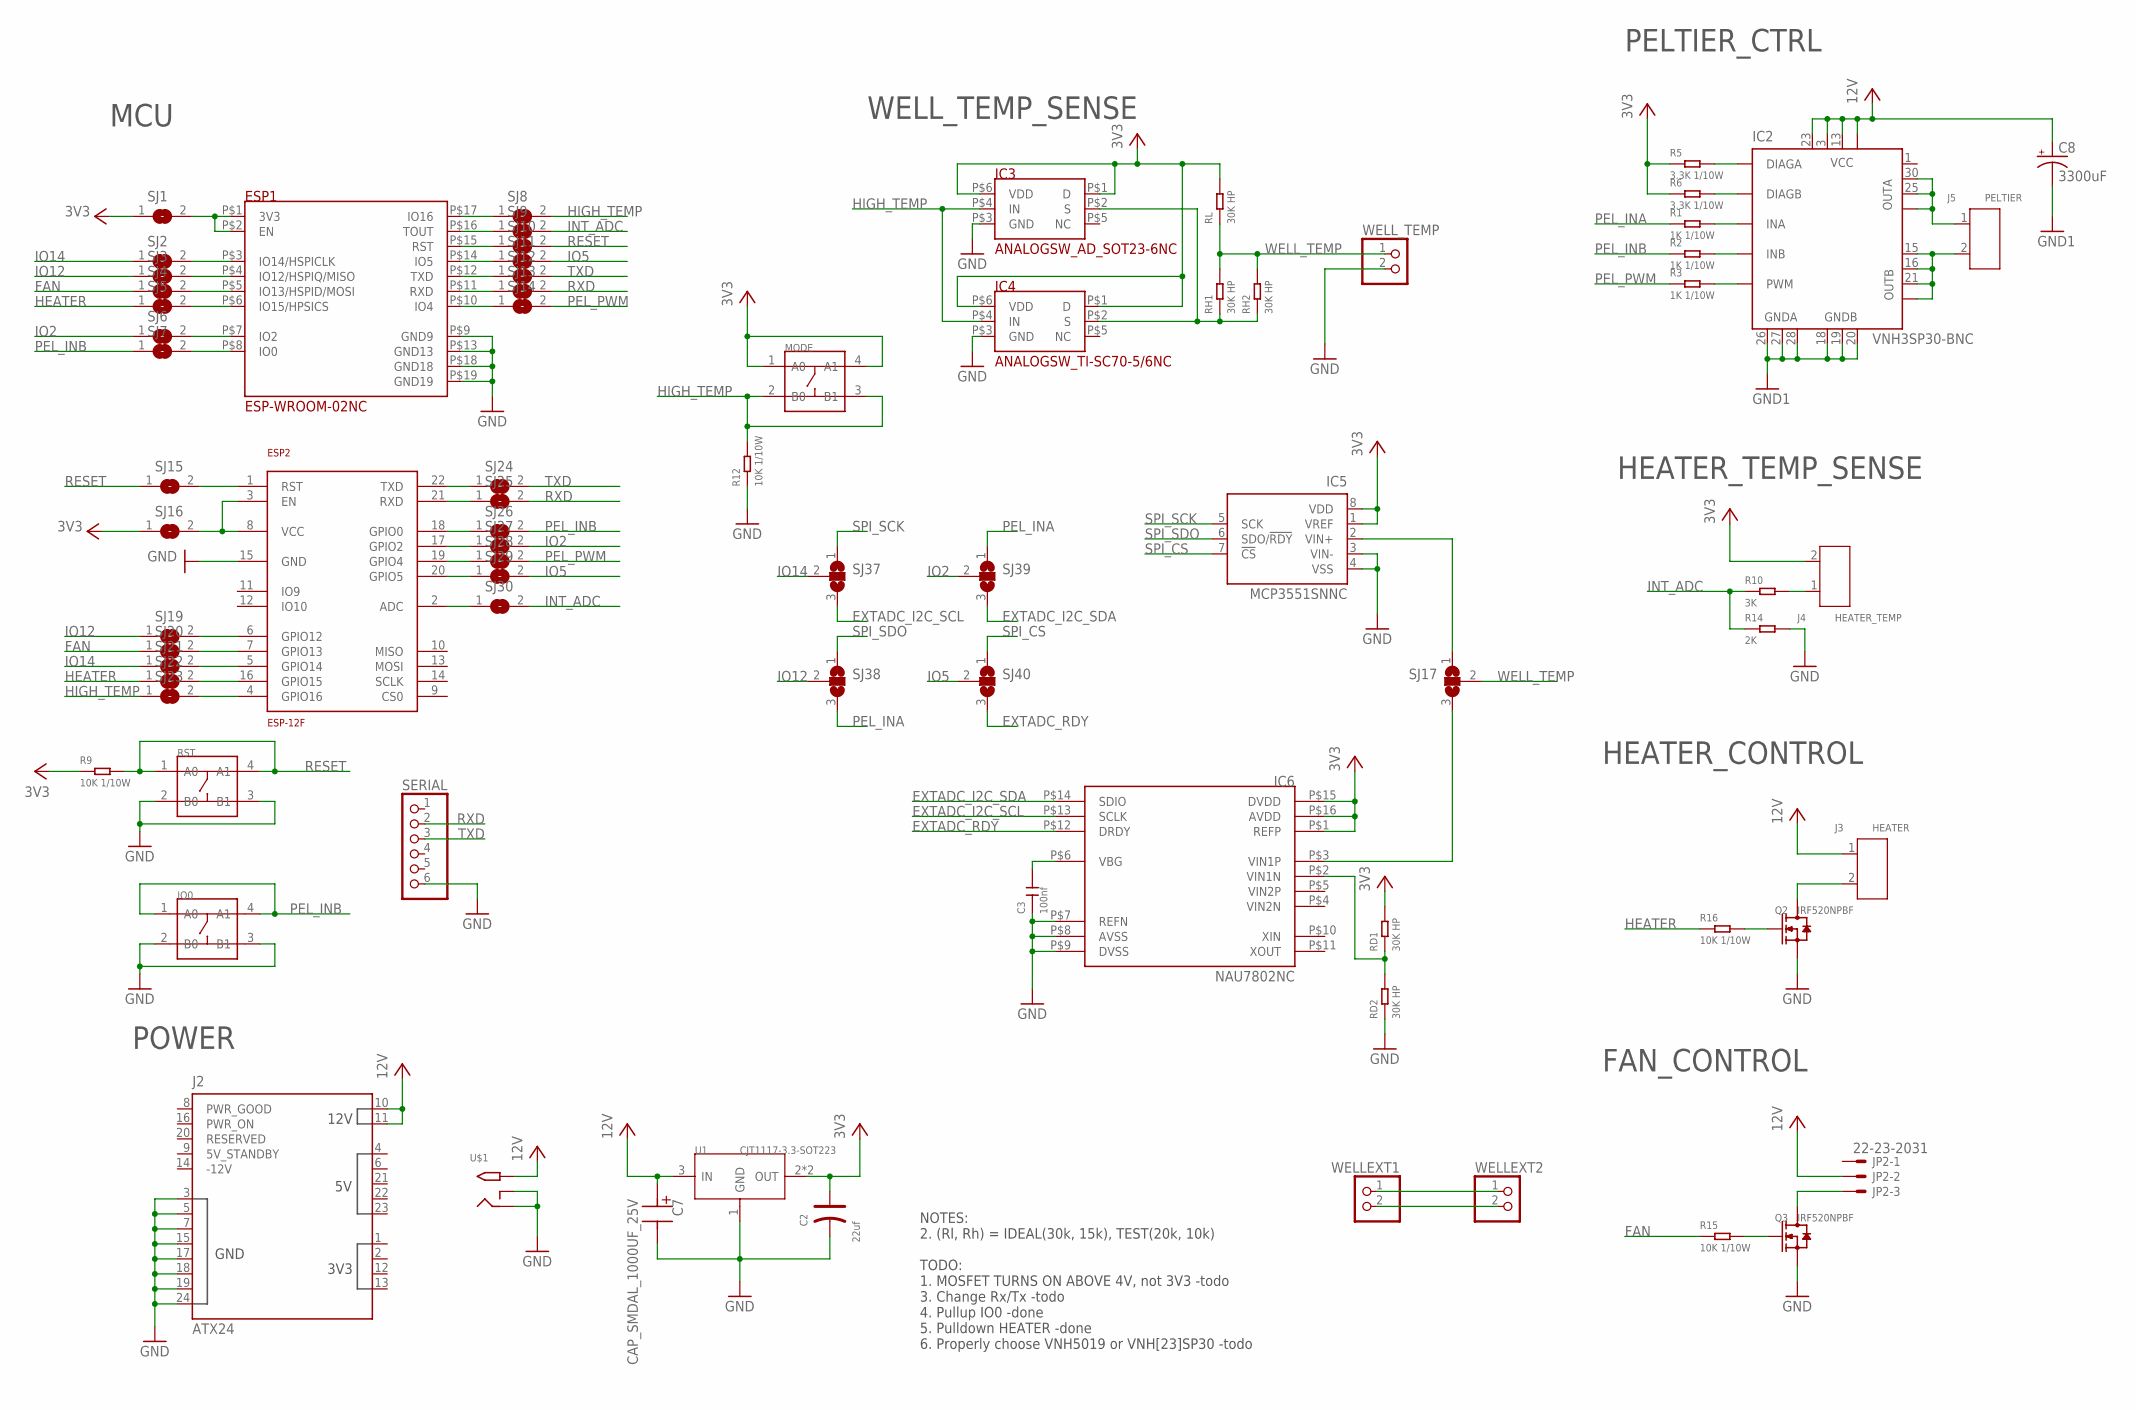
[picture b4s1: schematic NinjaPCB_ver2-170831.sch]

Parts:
C2: 22uf; AVX-B
C3: 100nf; C0603
C7: CAP_SMDAL_1000UF_25V; CAP_SMD_AL_D125
C8: 3300uF; E5-13-L30R-INV
ESP1: ESP-WROOM-02NC; ESP-WROOM-02-NOCREAM
ESP2: ESP-12F
IC2: VNH3SP30-BNC; MULTIPOWERSO-30-B-NOCREAM
IC3: ANALOGSW_AD_SOT23-6NC; SOT-23-6NC
IC4: ANALOGSW_TI-SC70-5/6NC; SC70-6NC
IC5: MCP3551SNNC; SO-08-NOCREAM
IC6: NAU7802NC; SOP-16NC
IO0: DIP-SWITCH-TACTILE-SPST-NO/TS-1109(4P-D6.0MM)'TS-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; SW4-6.0X6.0X5.0MM
J2: ATX24
J3: HEATER; H2-3.5-7.0X7.0MM
J4: HEATER_TEMP; H2-3.5-7.0X7.0MM
J5: PELTIER; H2-3.5-7.0X7.0MM
JP2: 22-23-2031
MODE: DIP-SWITCH-TACTILE-SPST-NO/TS-1109(4P-D6.0MM)'TS-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; SW4-6.0X6.0X5.0MM
Q2, Q3: IRF520NPBF; TO-220
R1, R2, R3: 1K 1/10W; R0603
R5, R6: 3.3K 1/10W; R0603
R9, R12, R15, R16: 10K 1/10W; R0603
R10: 3K; R0603
R14: 2K; R0603
RD1, RD2: 30K HP; R0603NC
RH1, RH2: 30K HP; R0603NC
RL: 30K HP; R0603NC
RST: DIP-SWITCH-TACTILE-SPST-NO/TS-1109(4P-D6.0MM)'TS-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; SW4-6.0X6.0X5.0MM
SERIAL: PINHD-1X6; 1X06
SJ1, SJ2, SJ3, SJ4, SJ5, SJ6, SJ7, SJ8, SJ9, SJ10, SJ11, SJ12, SJ13, SJ14, SJ15, SJ16, SJ19, SJ20, SJ21, SJ22, SJ23, SJ24, SJ25, SJ26, SJ27, SJ28, SJ29, SJ30: SJ
SJ17, SJ37, SJ38, SJ39, SJ40: SJ2W; SJ_2
U1: CJT1117-3.3-SOT223; SOT-223
U$1: 2.1MMJACKTHM; PJ-102A
WELLEXT1, WELLEXT2: PINHD-1X2; 1X02
WELL_TEMP: PINHD-1X2; 1X02

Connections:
3V3: C2.+, IC3.P$1 (D), IC3.P$6 (VDD), IC4.P$1 (D), IC4.P$6 (VDD), IC5.1 (VREF), IC5.8 (VDD), IC6.P$1 (REFP), IC6.P$15 (DVDD), IC6.P$16 (AVDD), J4.2, MODE.1 (A0), MODE.4 (A1), R5.1, R6.1, R9.1, RD1.2, RL.2, SJ1.1, SJ16.1, U1.2 (OUT), U1.TER (OUT)
12V: C7.P$P, C8.+, IC2.3 (VCC), IC2.13 (VCC), IC2.23 (VCC), IC2.VCC, J2.10 (12V_10), J2.11 (12V_11), J3.1, JP2.2, U1.3 (IN), U$1.TIP
EXTADC_I2C_SCL: IC6.P$13 (SCLK), SJ37.3
EXTADC_I2C_SDA: IC6.P$14 (SDIO), SJ39.3
EXTADC_RDY: IC6.P$12 (DRDY), SJ40.3
FAN: R15.1, SJ4.1, SJ20.1
GND: C2.-, C3.1, C7.P$M, C8.-, ESP1.P$9 (GND9), ESP1.P$13 (GND13), ESP1.P$18 (GND18), ESP1.P$19 (GND19), ESP2.15 (GND), IC2.18 (GNDB), IC2.19 (GNDB), IC2.20 (GNDB), IC2.26 (GNDA), IC2.27 (GNDA), IC2.28 (GNDA), IC3.P$3 (GND), IC4.P$3 (GND), IC5.3 (VIN-), IC5.4 (VSS), IC6.P$7 (REFN), IC6.P$8 (AVSS), IC6.P$9 (DVSS), IO0.2 (B0), IO0.3 (B1), J2.3 (GND3), J2.5 (GND5), J2.7 (GND7), J2.15 (GND15), J2.17 (GND17), J2.18 (GND18), J2.19 (GND19), J2.24 (GND24), Q2.2 (S), Q2.HEAT (S), Q3.2 (S), Q3.HEAT (S), R12.1, R14.2, RD2.1, RST.2 (B0), RST.3 (B1), SERIAL.6, U1.1 (GND), U$1.RING, U$1.RING_SW, WELL_TEMP.2
HEATER: R16.1, SJ5.1, SJ22.1
HIGH_TEMP: IC3.P$4 (IN), IC4.P$4 (IN), MODE.2 (B0), MODE.3 (B1), R12.2, SJ8.2, SJ23.1
I2C_WELL_TEMP: IC6.P$3 (VIN1P), SJ17.3
INT_ADC: R10.1, R14.1, SJ9.2, SJ30.2
IO2: SJ6.1, SJ27.2, SJ39.2
IO5: SJ11.2, SJ29.2, SJ40.2
IO12: SJ3.1, SJ19.1, SJ38.2
IO14: SJ2.1, SJ21.1, SJ37.2
unnamed: J4.1, R10.2
unnamed: J3.2, Q2.3 (D)
unnamed: Q2.1 (G), R16.2
unnamed: JP2.3, Q3.3 (D)
unnamed: Q3.1 (G), R15.2
unnamed: IC2.6 (DIAGA), R5.2
unnamed: IC2.10 (DIAGB), R6.2
unnamed: IC2.5 (INA), R1.2
unnamed: IC2.11 (INB), R2.2
unnamed: IC2.8 (PWM), R3.2
unnamed: ESP1.P$1 (3V3), ESP1.P$2 (EN), SJ1.2
unnamed: ESP1.P$3 (IO14/HSPICLK), SJ2.2
unnamed: ESP1.P$4 (IO12/HSPIQ/MISO), SJ3.2
unnamed: ESP1.P$5 (IO13/HSPID/MOSI), SJ4.2
unnamed: ESP1.P$6 (IO15/HPSICS), SJ5.2
unnamed: ESP1.P$7 (IO2), SJ6.2
unnamed: ESP1.P$8 (IO0), SJ7.2
unnamed: ESP1.P$17 (IO16), SJ8.1
unnamed: ESP1.P$16 (TOUT), SJ9.1
unnamed: ESP1.P$15 (RST), SJ10.1
unnamed: ESP1.P$14 (IO5), SJ11.1
unnamed: ESP1.P$12 (TXD), SJ12.1
unnamed: ESP1.P$11 (RXD), SJ13.1
unnamed: ESP1.P$10 (IO4), SJ14.1
unnamed: WELLEXT1.1, WELLEXT2.1
unnamed: IC3.P$2 (S), IC4.P$2 (S), RH1.1, RH2.1
unnamed: WELLEXT1.2, WELLEXT2.2
unnamed: ESP2.1 (RST), SJ15.2
unnamed: ESP2.3 (EN), ESP2.8 (VCC), SJ16.2
unnamed: ESP2.22 (TXD), SJ24.1
unnamed: ESP2.21 (RXD), SJ25.1
unnamed: ESP2.18 (GPIO0), SJ26.1
unnamed: ESP2.17 (GPIO2), SJ27.1
unnamed: ESP2.19 (GPIO4), SJ28.1
unnamed: ESP2.20 (GPIO5), SJ29.1
unnamed: ESP2.2 (ADC), SJ30.1
unnamed: ESP2.6 (GPIO12), SJ19.2
unnamed: ESP2.7 (GPIO13), SJ20.2
unnamed: ESP2.5 (GPIO14), SJ21.2
unnamed: ESP2.16 (GPIO15), SJ22.2
unnamed: ESP2.4 (GPIO16), SJ23.2
unnamed: IC6.P$2 (VIN1N), RD1.1, RD2.2
unnamed: C3.2, IC6.P$6 (VBG)
OUTA: IC2.25 (OUTA), IC2.30 (OUTA), IC2.OUTA, J5.1
OUTB: IC2.15 (OUTB), IC2.16 (OUTB), IC2.21 (OUTB), IC2.OUTB, J5.2
PEL_INA: R1.1, SJ38.3, SJ39.1
PEL_INB: IO0.1 (A0), IO0.4 (A1), R2.1, SJ7.1, SJ26.2
PEL_PWM: R3.1, SJ14.2, SJ28.2
RESET: R9.2, RST.1 (A0), RST.4 (A1), SJ10.2, SJ15.1
RXD: SERIAL.2, SJ13.2, SJ25.2
SPI_CS: IC5.7 (!CS), SJ40.1
SPI_SCK: IC5.5 (SCK), SJ37.1
SPI_SDO: IC5.6 (SDO/!RDY), SJ38.1
SPI_WELL_TEMP: IC5.2 (VIN+), SJ17.1
TXD: SERIAL.3, SJ12.2, SJ24.2
WELL_TEMP: RH1.2, RH2.2, RL.1, SJ17.2, WELL_TEMP.1

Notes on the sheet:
WELL_TEMP_SENSE
HEATER_TEMP_SENSE
HEATER_CONTROL
FAN_CONTROL
PELTIER_CTRL
MCU
POWER
NOTES: 2. (Rl, Rh) = IDEAL(30k, 15k), TEST(20k, 10k) TODO: 1. MOSFET TURNS ON ABOVE 4V, not 3V3 -todo 3. Change Rx/Tx -todo 4. Pullup IO0 -done 5. Pulldown HEATER -done 6. Properly choose VNH5019 or VNH[23]SP30 -todo
